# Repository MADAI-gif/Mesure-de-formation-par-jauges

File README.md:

# Mesure de Déformation par Jauges – Dispositif de Commande Haptique

## 📌 Description du projet
Ce projet a pour objectif de concevoir un **système de commande haptique** basé sur la mesure de déformation d’une lame métallique.  
Quatre jauges de déformation, montées en **pont de Wheatstone**, sont fixées sur la lame afin de mesurer les contraintes appliquées.  
Le signal issu du pont est amplifié par un **AD624** (carte de puissance) puis lu par une carte **Nucleo STM32** via l’entrée analogique PA0.  
Le traitement embarqué permet d’estimer la force appliquée et de piloter un **moteur pas à pas** en asservissement de position.

---

## 🎯 Objectifs
- Concevoir un système de mesure haptique fiable et précis.  
- Assurer la cohérence entre la force appliquée et le mouvement du moteur.  
- Calibrer le système pour obtenir une relation linéaire entre la tension mesurée et la déformation.  
- Valider le bon fonctionnement par comparaison entre résultats théoriques et expérimentaux.

---

## 🛠 Réalisations techniques
- **Capteur** : 4 jauges de déformation en pont de Wheatstone.  
- **Conditionnement du signal** : Amplificateur AD624.  
- **Acquisition** : Carte Nucleo STM32 (entrée analogique PA0).  
- **Actionneur** : Moteur pas à pas commandé en position.  
- **Interface Homme-Machine (IHM)** pour le suivi en temps réel.  
- **Carte de puissance** dédiée.  

---

## 📐 Méthodologie
1. **Montage mécanique** : fixation des jauges sur la lame métallique.  
2. **Montage électronique** : pont de Wheatstone → amplification analogique → acquisition STM32.  
3. **Calibration** : série de tests pour établir la relation tension–force–déformation.  
4. **Traitement logiciel** : calcul de la force appliquée et pilotage du moteur pas à pas.  
5. **Validation** : comparaison avec le modèle théorique.

---

## 📊 Résultats
- Relation linéaire observée entre tension mesurée et déformation/poids appliqué.  
- Écart faible entre théorie et expérience (dus aux pertes et imprécisions expérimentales).  
- Bonne réactivité et positionnement précis du moteur pas à pas.  
- Système fiable et stable lors des essais.

---

## 🔭 Perspectives
- Miniaturisation du dispositif.  
- Intégration d’un **retour de force** pour applications médicales ou aéronautiques.  
- Optimisation de l’IHM et du traitement embarqué.  

---

## 👥 Équipe
- Alexandre P.  
- Mathieu L.  
- Yvan M.  
- Madaï M.

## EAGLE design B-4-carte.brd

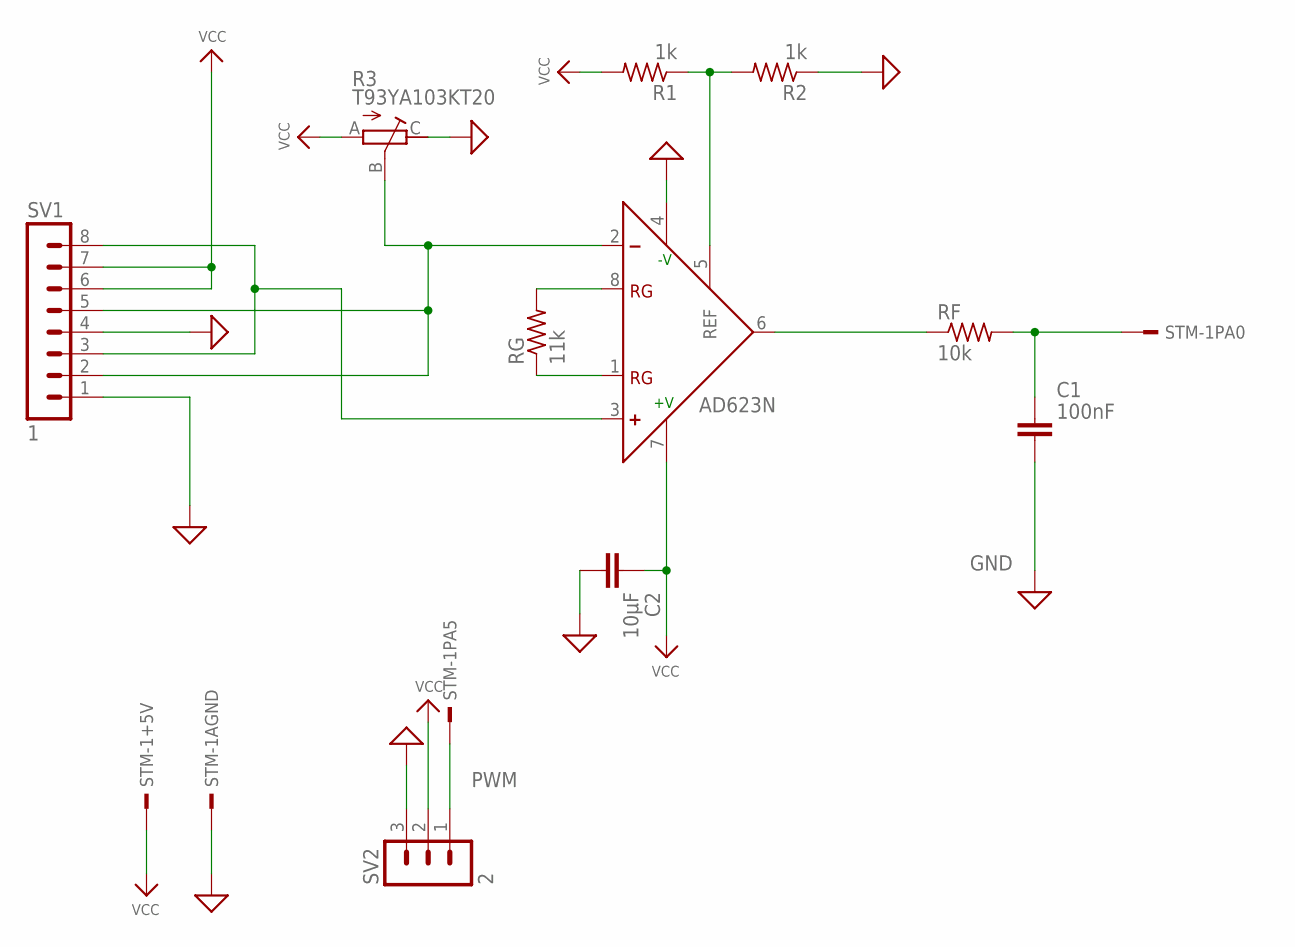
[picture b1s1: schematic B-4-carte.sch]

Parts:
C1: 100nF; C2.5-2
C2: 10µF; C2.5-2
IC1: AD623N; DIL08
R1, R2: 1k; 0204/7
R3: T93YA103KT20; TRIM_T93YA103KT20
RF: 10k; 0204/7
RG: 11k; 0204/7
STM-1: NUCLEO-F411RE; CONN_STM32_NUCLEO
SV1: 1; MA08-1
SV2: 2; MA03-1

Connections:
GND: C1.2, C2.2, IC1.4 (-V), R2.1, R3.C, STM-1.70, SV1.1, SV1.4, SV2.3
unnamed: IC1.3 (+), SV1.3, SV1.8
unnamed: C1.1, RF.2, STM-1.28
unnamed: IC1.2 (-), R3.B, SV1.2, SV1.5
unnamed: IC1.1 (RG), RG.1
unnamed: IC1.8 (RG), RG.2
unnamed: IC1.5 (REF), R1.1, R2.2
unnamed: IC1.6 (OUT), RF.1
PWM: STM-1.49, SV2.1
VCC: C2.1, IC1.7 (+V), R1.2, R3.A, STM-1.18, SV1.6, SV1.7, SV2.2

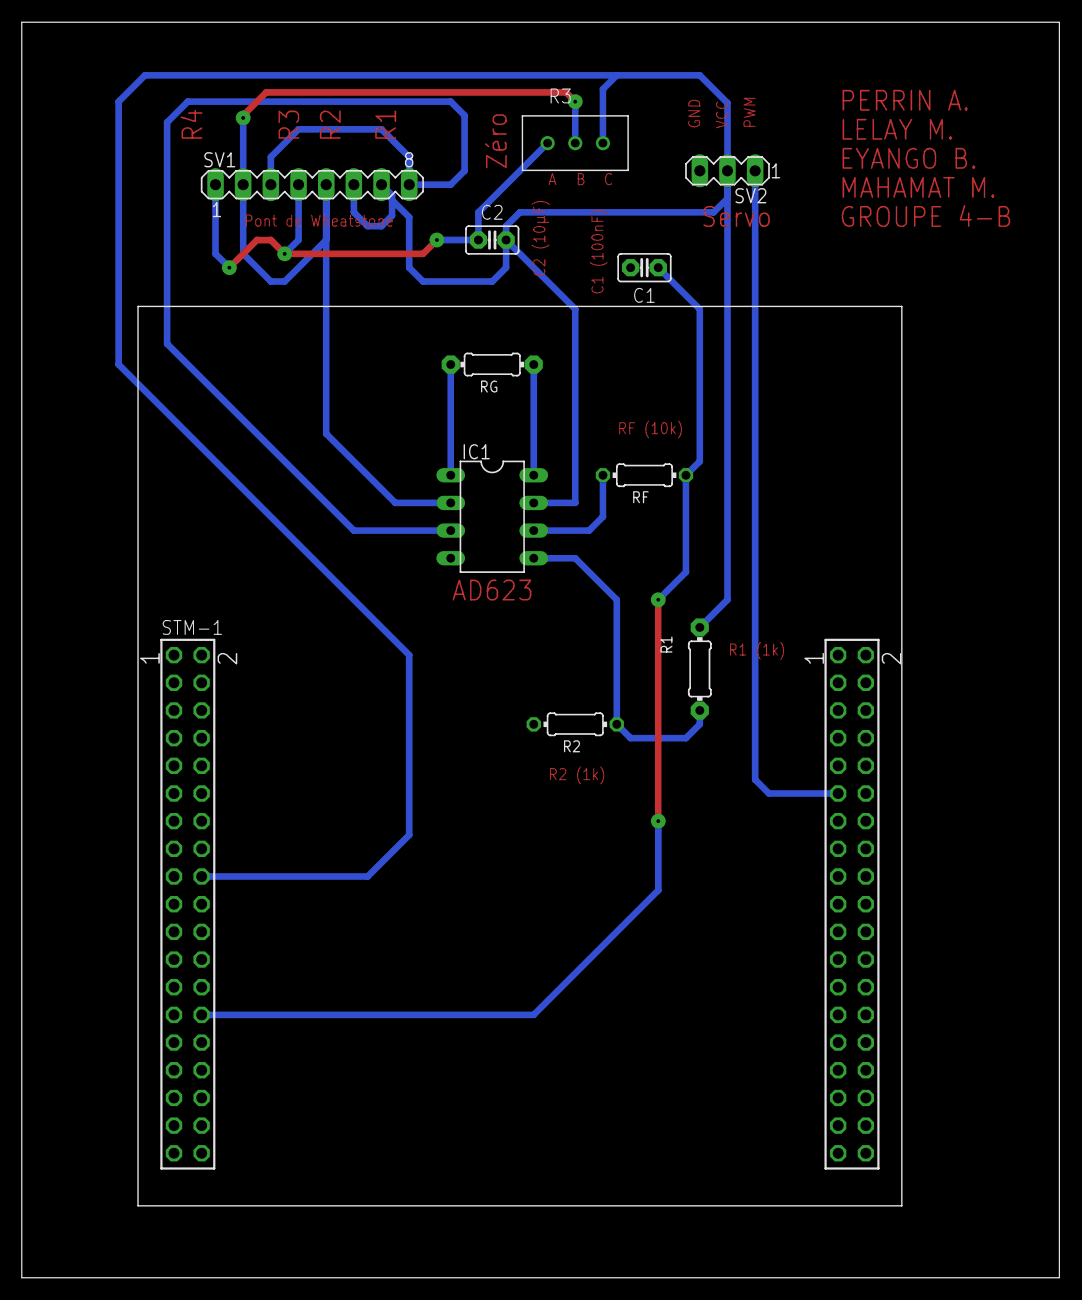
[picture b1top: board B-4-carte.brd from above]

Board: 2 copper layers, 95.2 x 115.2 mm, 11 parts (0 on the bottom side), 10 nets.

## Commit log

2025-08-13 deformation par jauges
